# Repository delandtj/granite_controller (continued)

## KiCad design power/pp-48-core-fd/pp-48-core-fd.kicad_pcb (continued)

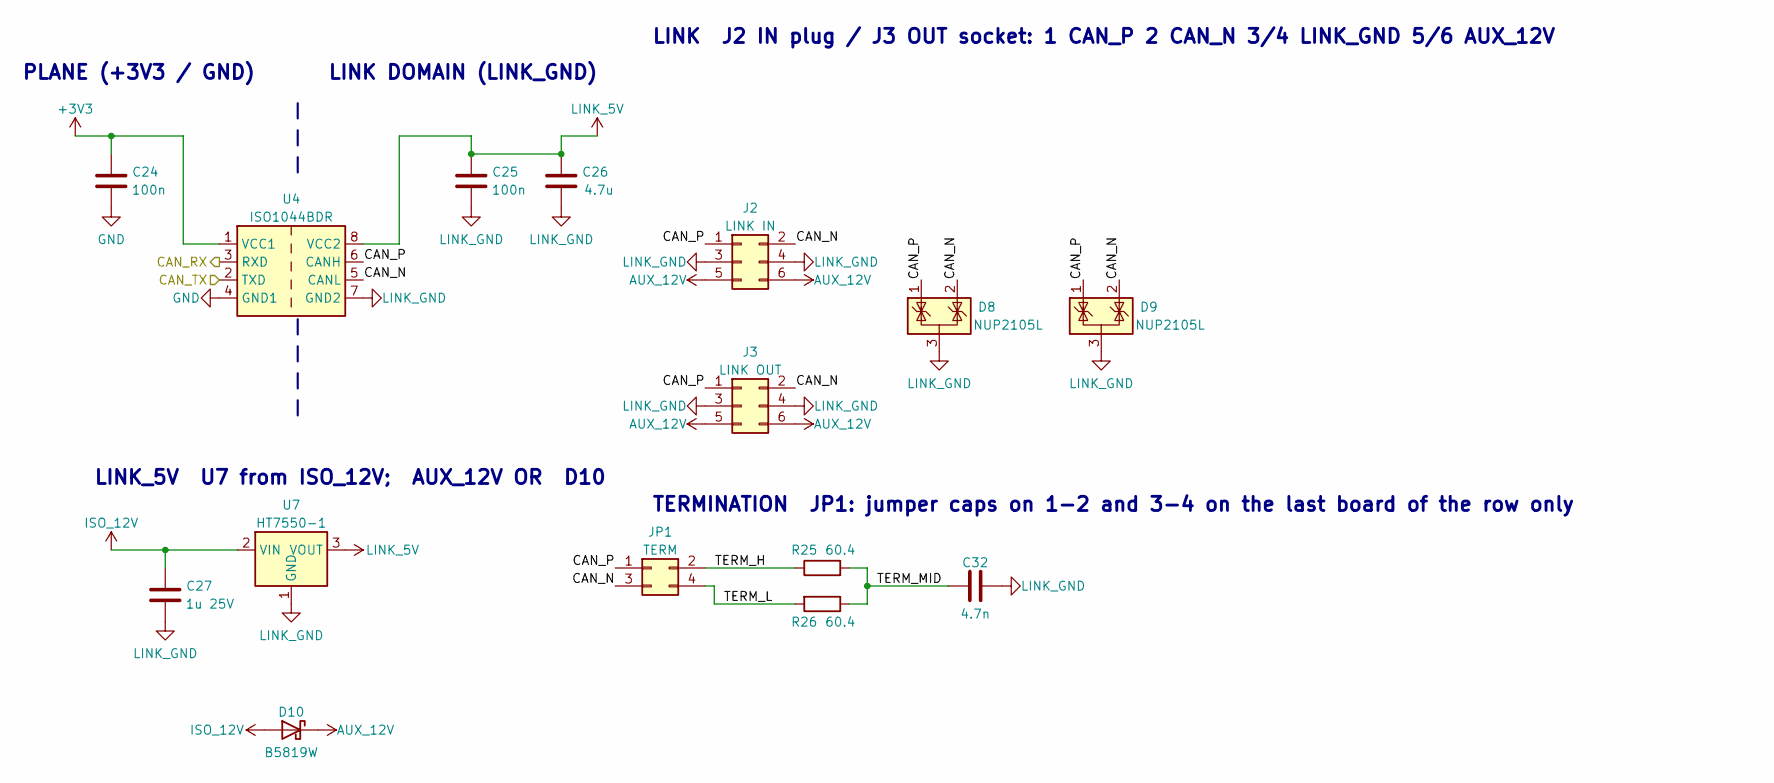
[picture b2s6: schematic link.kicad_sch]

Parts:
C24, C25: 100n; C_0402_1005Metric; MPN Samsung CL05B104KO5NNNC; LCSC C1525
C26: 4.7u; C_0603_1608Metric; MPN Samsung CL10A475KO8NNNC; LCSC C19666
C27: 1u 25V; C_0603_1608Metric; MPN Samsung CL10A105KB8NNNC; LCSC C15849
C32: 4.7n; C_0402_1005Metric; MPN FH 0402B472K500NT; LCSC C1538
D8, D9: NUP2105L; SOT-23; MPN onsemi NUP2105LT1G; LCSC C14486
D10: B5819W; D_SOD-123; MPN SL B5819W; LCSC C8598
J2: LINK IN; PinHeader_2x03_P2.54mm_Horizontal; MPN CJT A2541WR-2x3P; LCSC C239334
J3: LINK OUT; PinSocket_2x03_P2.54mm_Horizontal; MPN CJT A2541HWR-2x3P; LCSC C5333425
JP1: TERM; PinHeader_2x02_P2.54mm_Vertical; MPN XFCN PZ254V-12-4P; LCSC C492419
R25, R26: 60.4; R_0603_1608Metric; MPN Yageo AC0603FR-0760R4L; LCSC C144645
U4: ISO1044BDR; SOIC-8_3.9x4.9mm_P1.27mm; MPN TI ISO1044BDR; LCSC C2878225
U7: HT7550-1; SOT-89-3; MPN Holtek HT7550-1; LCSC C16106

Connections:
+3V3: C24.1, U4.1 (VCC1); also elsewhere on the board
/CAN_RX: U4.3 (RXD); also elsewhere on the board
/CAN_TX: U4.2 (TXD); also elsewhere on the board
/Link/CAN_N: D8.2 (K), D9.2 (K), J2.2, J3.2, JP1.3, U4.5 (CANL)
/Link/CAN_P: D8.1 (K), D9.1 (K), J2.1, J3.1, JP1.1, U4.6 (CANH)
/Link/TERM_H: JP1.2, R25.1
/Link/TERM_L: JP1.4, R26.2
/Link/TERM_MID: C32.1, R25.2, R26.1
AUX_12V: D10.1 (K), J2.5, J2.6, J3.5, J3.6
GND: C24.2, U4.4 (GND1); also elsewhere on the board
ISO_12V: C27.1, D10.2 (A), U7.2 (VIN); also elsewhere on the board
LINK_5V: C25.1, C26.1, U4.8 (VCC2), U7.3 (VOUT)
LINK_GND: C25.2, C26.2, C27.2, C32.2, D8.3 (A), D9.3 (A), J2.3, J2.4, J3.3, J3.4, U4.7 (GND2), U7.1 (GND); also elsewhere on the board

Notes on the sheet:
LINK_5V U7 from ISO_12V; AUX_12V OR D10
PLANE (+3V3 / GND)
LINK DOMAIN (LINK_GND)
LINK J2 IN plug / J3 OUT socket: 1 CAN_P 2 CAN_N 3/4 LINK_GND 5/6 AUX_12V
TERMINATION JP1: jumper caps on 1-2 and 3-4 on the last board of the row only

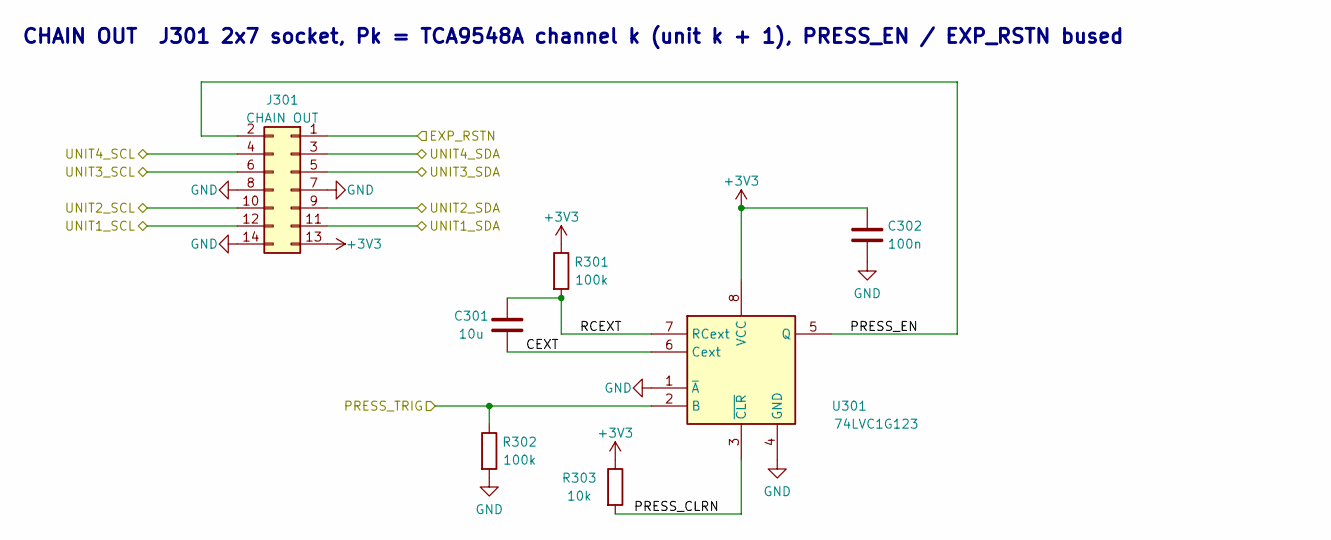
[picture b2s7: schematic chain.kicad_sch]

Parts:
C301: 10u; C_0805_2012Metric; LCSC C15850
C302: 100n; C_0402_1005Metric; LCSC C1525
J301: CHAIN OUT; PinSocket_2x07_P2.54mm_Horizontal; MPN CJT A2541HWR-2x7P; LCSC C19100281
R301, R302: 100k; R_0402_1005Metric; LCSC C25741
R303: 10k; R_0402_1005Metric; LCSC C25744
U301: 74LVC1G123; SSOP-8_2.95x2.8mm_P0.65mm; MPN TI SN74LVC1G123DCTR; LCSC C123302

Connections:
+3V3: C302.1, J301.13, R301.1, R303.1, U301.8 (VCC); also elsewhere on the board
/Chain/CEXT: C301.2, U301.6 (Cext)
/Chain/PRESS_CLRN: R303.2, U301.3 (~CLR)
/Chain/PRESS_EN: J301.2, U301.5 (Q)
/Chain/RCEXT: C301.1, R301.2, U301.7 (RCext)
/EXP_RSTN: J301.1; also elsewhere on the board
/PRESS_TRIG: R302.1, U301.2 (B); also elsewhere on the board
/UNIT1_SCL: J301.12; also elsewhere on the board
/UNIT1_SDA: J301.11; also elsewhere on the board
/UNIT2_SCL: J301.10; also elsewhere on the board
/UNIT2_SDA: J301.9; also elsewhere on the board
/UNIT3_SCL: J301.6; also elsewhere on the board
/UNIT3_SDA: J301.5; also elsewhere on the board
/UNIT4_SCL: J301.4; also elsewhere on the board
/UNIT4_SDA: J301.3; also elsewhere on the board
GND: C302.2, J301.7, J301.8, J301.14, R302.2, U301.1 (~A), U301.4 (GND); also elsewhere on the board

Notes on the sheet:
CHAIN OUT J301 2x7 socket, Pk = TCA9548A channel k (unit k + 1), PRESS_EN / EXP_RSTN bused

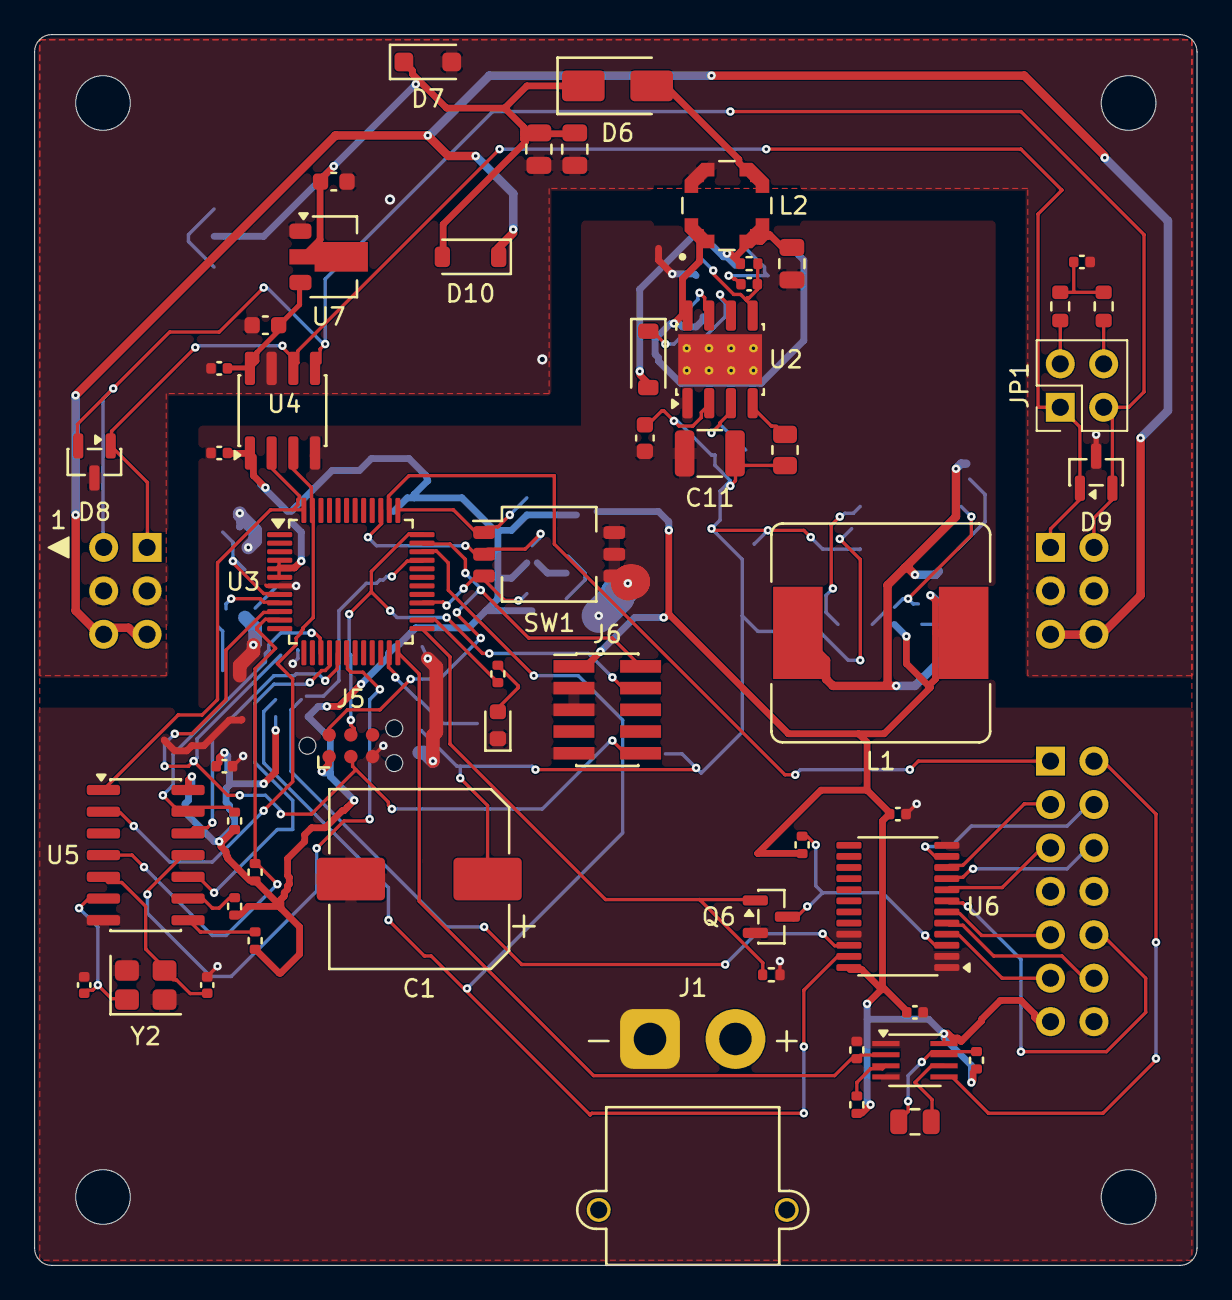
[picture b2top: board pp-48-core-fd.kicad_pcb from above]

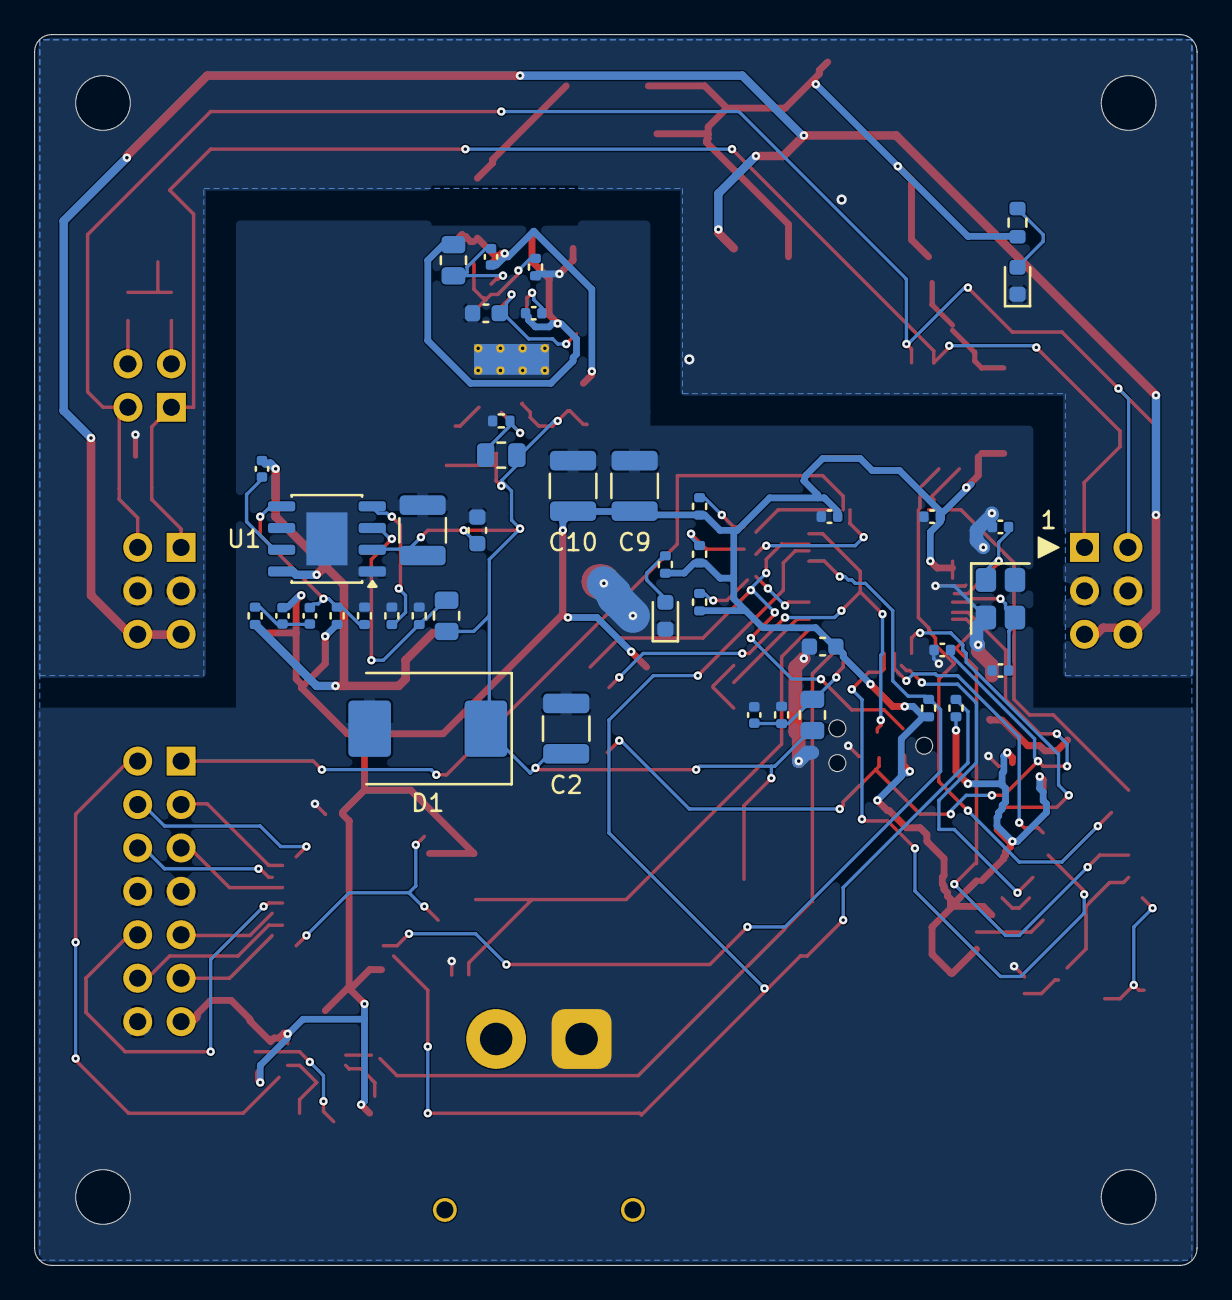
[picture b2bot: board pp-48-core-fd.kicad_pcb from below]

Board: 4 copper layers, 68.0 x 72.0 mm, 104 parts (45 on the bottom side), 69 nets.

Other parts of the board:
H1, H2, H3, H4: MountingHole_3.2mm_M3

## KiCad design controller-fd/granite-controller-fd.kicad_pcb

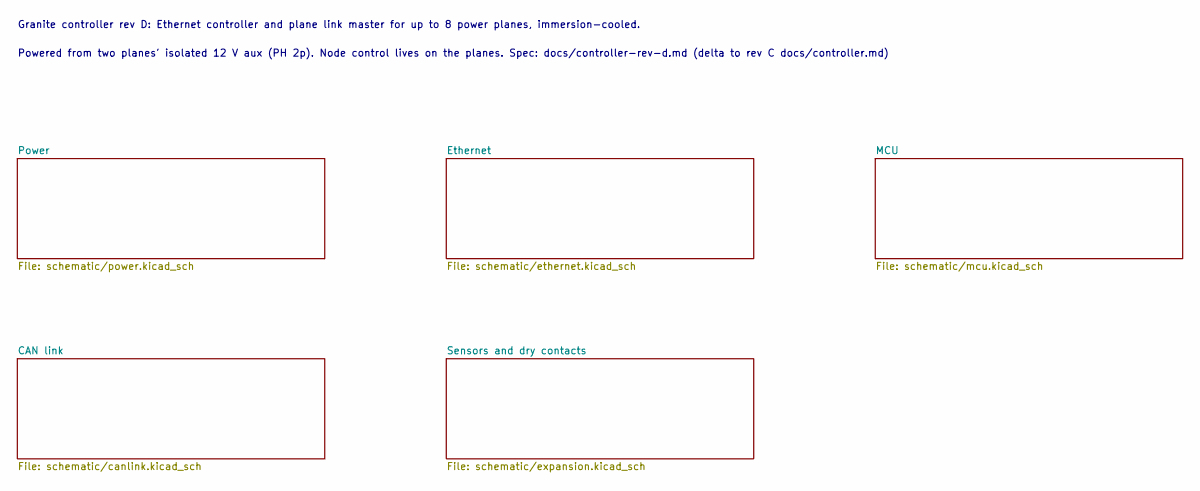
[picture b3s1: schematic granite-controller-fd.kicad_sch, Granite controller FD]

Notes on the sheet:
Granite controller rev D: Ethernet controller and plane link master for up to 8 power planes, immersion-cooled.
Powered from two planes' isolated 12 V aux (PH 2p). Node control lives on the planes. Spec: docs/controller-rev-d.md (delta to rev C docs/controller.md)

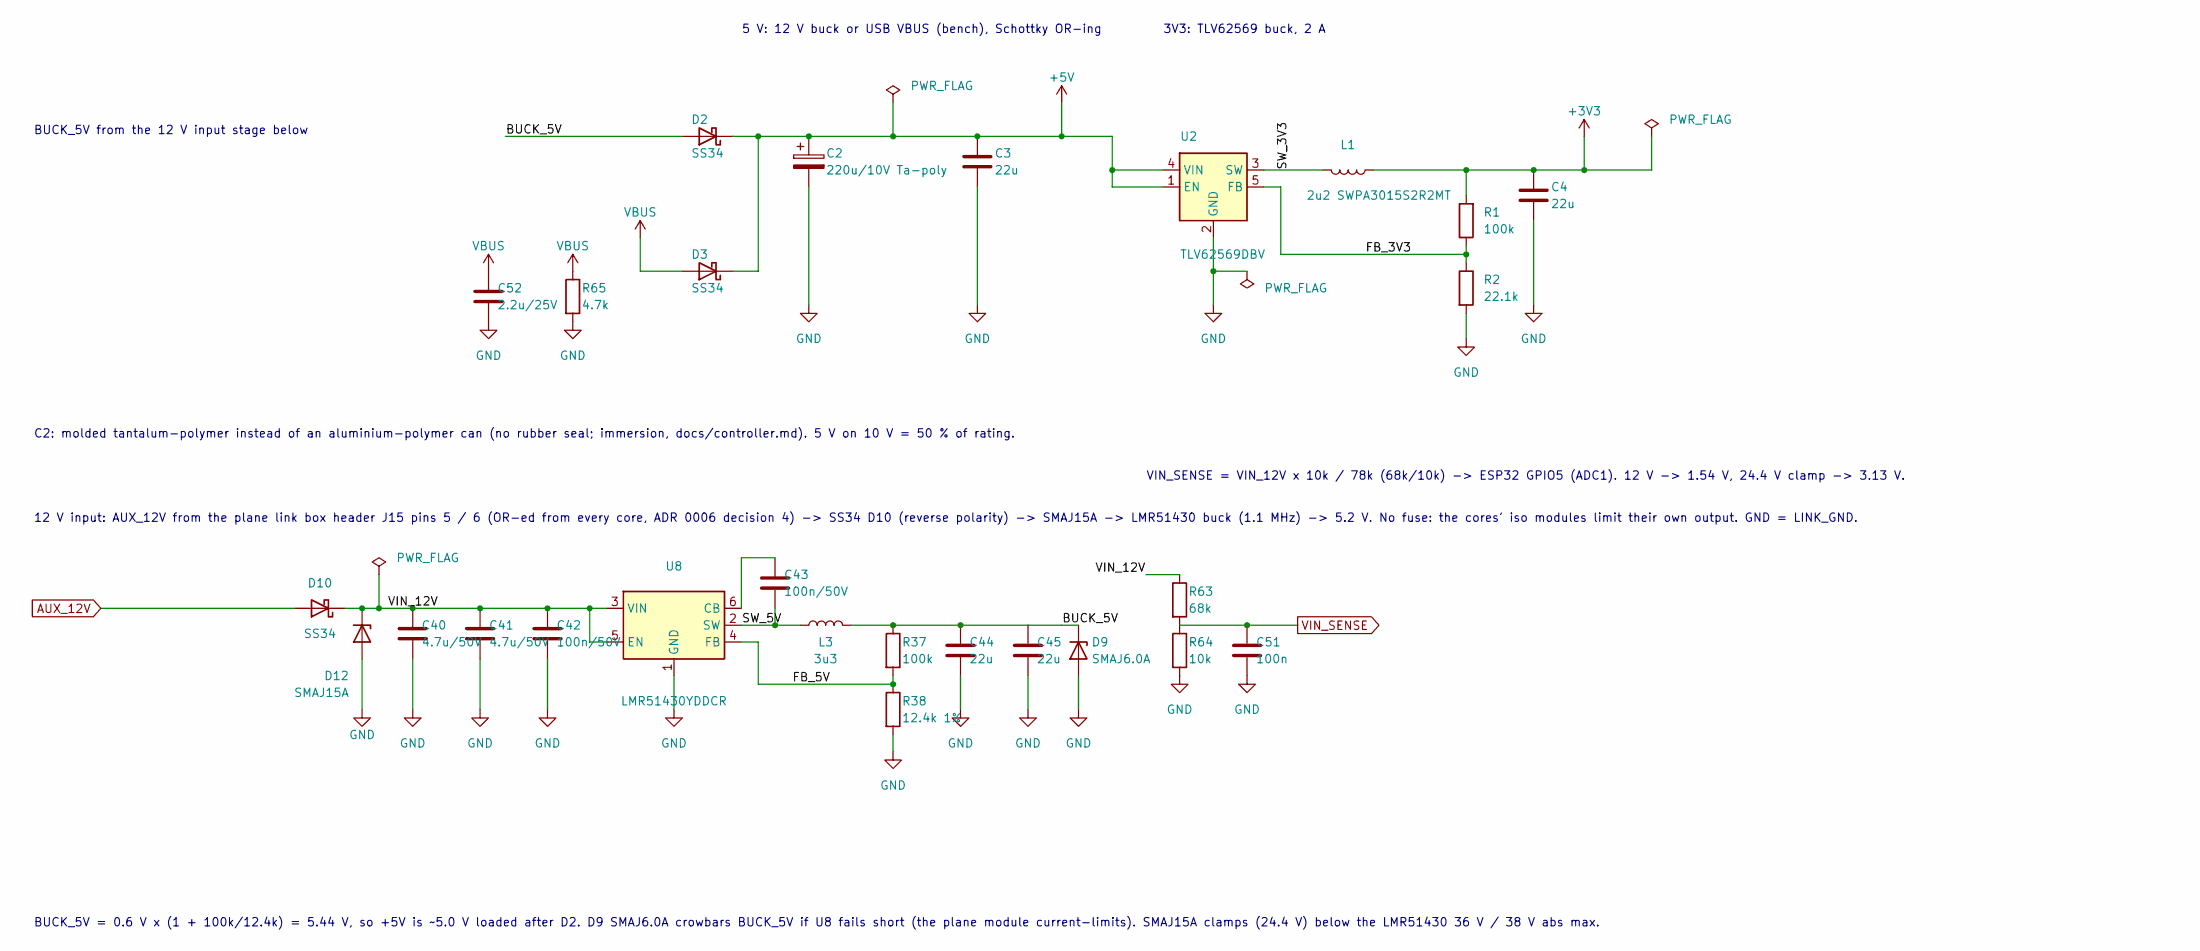
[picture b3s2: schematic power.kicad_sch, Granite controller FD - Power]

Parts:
C2: 220u/10V Ta-poly; CP_EIA-7343-31_Kemet-D; MPN T520D227M010ATE018; LCSC C116742
C3, C4, C44, C45: 22u; C_0805_2012Metric; MPN CL21A226MAQNNNE; LCSC C45783
C40, C41: 4.7u/50V; C_1206_3216Metric; MPN 1206B475K500NT; LCSC C29823
C42, C43: 100n/50V; C_0402_1005Metric; MPN CL05B104KB54PNC; LCSC C307331
C51: 100n; C_0402_1005Metric; MPN CL05B104KO5NNNC; LCSC C1525
C52: 2.2u/25V; C_0603_1608Metric; MPN CL10A225KA8NNNC; LCSC C57895
D2, D3, D10: SS34; D_SMA; MPN SS34; LCSC C8678
D9: SMAJ6.0A; D_SMA; MPN SMAJ6.0A; LCSC C364284
D12: SMAJ15A; D_SMA; MPN SMAJ15A; LCSC C148216
L1: 2u2 SWPA3015S2R2MT; L_Sunlord_SWPA3015S; MPN SWPA3015S2R2MT; LCSC C43389
L3: 3u3; L_Changjiang_FXL0630; MPN FXL0630-3R3-M; LCSC C167219
R1, R37: 100k; R_0402_1005Metric; MPN 0402WGF1003TCE; LCSC C25741
R2: 22.1k; R_0402_1005Metric; MPN RC0402FR-0722K1L; LCSC C163478
R38: 12.4k 1%; R_0402_1005Metric; MPN 0402WGF1242TCE; LCSC C11692
R63: 68k; R_0402_1005Metric; MPN 0402WGF6802TCE; LCSC C36871
R64: 10k; R_0402_1005Metric; MPN 0402WGF1002TCE; LCSC C25744
R65: 4.7k; R_0402_1005Metric; MPN 0402WGF4701TCE; LCSC C25900
U2: TLV62569DBV; SOT-23-5; MPN TLV62569DBVR; LCSC C141836
U8: LMR51430YDDCR; SOT-23-6; MPN LMR51430YDDCR; LCSC C5210749

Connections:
+3V3: C4.1, L1.1, R1.2; also elsewhere on the board
+5V: C2.1, C3.1, D2.1 (K), D3.1 (K), U2.1 (EN), U2.4 (VIN); also elsewhere on the board
/Power/BUCK_5V: C44.1, C45.1, D2.2 (A), D9.1 (K), L3.2, R37.1
/Power/FB_3V3: R1.1, R2.1, U2.5 (FB)
/Power/FB_5V: R37.2, R38.1, U8.4 (FB)
/Power/SW_3V3: L1.2, U2.3 (SW)
/Power/SW_5V: C43.2, L3.1, U8.2 (SW)
/Power/VIN_12V: C40.1, C41.1, C42.1, D10.1 (K), D12.1 (K), R63.1, U8.3 (VIN), U8.5 (EN)
AUX_12V: D10.2 (A); also elsewhere on the board
GND: C2.2, C3.2, C4.2, C40.2, C41.2, C42.2, C44.2, C45.2, C51.2, C52.2, D9.2 (A), D12.2 (A), R2.2, R38.2, R64.2, R65.2, U2.2 (GND), U8.1 (GND); also elsewhere on the board
unnamed: C43.1, U8.6 (CB)
VBUS: C52.1, D3.2 (A), R65.1; also elsewhere on the board
VIN_SENSE: C51.1, R63.2, R64.1; also elsewhere on the board

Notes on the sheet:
5 V: 12 V buck or USB VBUS (bench), Schottky OR-ing
3V3: TLV62569 buck, 2 A
BUCK_5V from the 12 V input stage below
12 V input: AUX_12V from the plane link box header J15 pins 5 / 6 (OR-ed from every core, ADR 0006 decision 4) -> SS34 D10 (reverse polarity) -> SMAJ15A -> LMR51430 buck (1.1 MHz) -> 5.2 V. No fuse: the cores' iso modules limit their own output. GND = LINK_GND.
BUCK_5V = 0.6 V x (1 + 100k/12.4k) = 5.44 V, so +5V is ~5.0 V loaded after D2. D9 SMAJ6.0A crowbars BUCK_5V if U8 fails short (the plane module current-limits). SMAJ15A clamps (24.4 V) below the LMR51430 36 V / 38 V abs max.
C2: molded tantalum-polymer instead of an aluminium-polymer can (no rubber seal; immersion, docs/controller.md). 5 V on 10 V = 50 % of rating.
VIN_SENSE = VIN_12V x 10k / 78k (68k/10k) -> ESP32 GPIO5 (ADC1). 12 V -> 1.54 V, 24.4 V clamp -> 3.13 V.

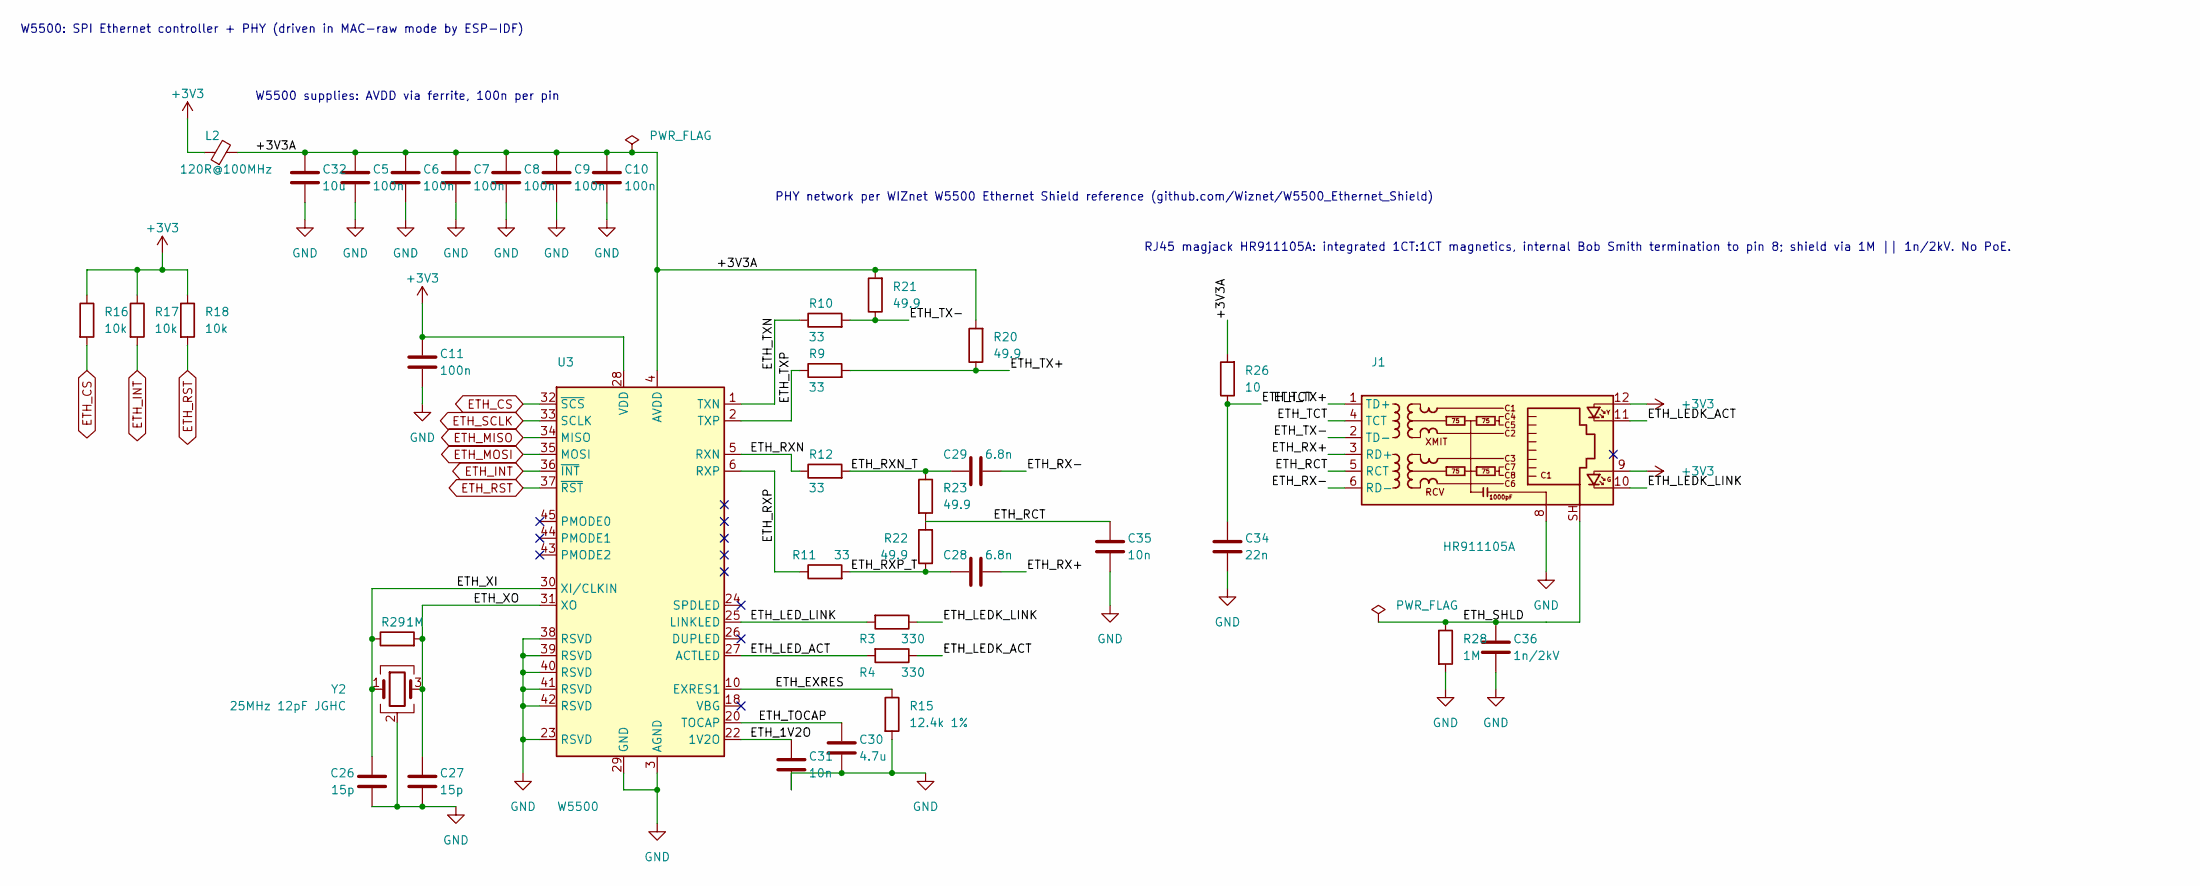
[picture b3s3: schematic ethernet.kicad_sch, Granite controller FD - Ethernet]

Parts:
C5, C6, C7, C8, C9, C10, C11: 100n; C_0402_1005Metric; MPN CL05B104KO5NNNC; LCSC C1525
C26, C27: 15p; C_0402_1005Metric; MPN 0402CG150J500NT; LCSC C1548
C28, C29: 6.8n; C_0402_1005Metric; MPN CC0402KRX7R9BB682; LCSC C93654
C30: 4.7u; C_0603_1608Metric; MPN CL10A475KO8NNNC; LCSC C19666
C31, C35: 10n; C_0402_1005Metric; MPN CL05B103KB5NNNC; LCSC C15195
C32: 10u; C_0805_2012Metric; MPN CL21A106KAYNNNE; LCSC C15850
C34: 22n; C_0402_1005Metric; MPN 0402B223K500NT; LCSC C1532
C36: 1n/2kV; C_1812_4532Metric; MPN CC1812KKX7RDBB102; LCSC C118019
J1: HR911105A; RJ45_Hanrun_HR911105A_Horizontal; MPN HR911105A; LCSC C12074
L2: 120R@100MHz; L_0603_1608Metric; MPN BLM18PG121SN1D; LCSC C14709
R3, R4: 330; R_0402_1005Metric; MPN 0402WGF3300TCE; LCSC C25104
R9, R10, R11, R12: 33; R_0402_1005Metric; MPN 0402WGF330JTCE; LCSC C25105
R15: 12.4k 1%; R_0402_1005Metric; MPN 0402WGF1242TCE; LCSC C11692
R16, R17, R18: 10k; R_0402_1005Metric; MPN 0402WGF1002TCE; LCSC C25744
R20, R21, R22, R23: 49.9; R_0402_1005Metric; MPN 0402WGF499JTCE; LCSC C25120
R26: 10; R_0402_1005Metric; MPN 0402WGF100JTCE; LCSC C25077
R28: 1M; R_0603_1608Metric; MPN 0603WAF1004T5E; LCSC C22935
R29: 1M; R_0402_1005Metric; MPN 0402WGF1004TCE; LCSC C26083
U3: W5500; LQFP-48_7x7mm_P0.5mm; MPN W5500; LCSC C32843
Y2: 25MHz 12pF JGHC; Crystal_SMD_Abracon_ABM8G-4Pin_3.2x2.5mm; MPN S3225000121060; LCSC C390773

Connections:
+3V3: C11.1, J1.9, J1.12, L2.1, R16.1, R17.1, R18.1, U3.28 (VDD); also elsewhere on the board
/Ethernet/+3V3A: C5.1, C6.1, C7.1, C8.1, C9.1, C10.1, C32.1, L2.2, R20.2, R21.2, R26.2, U3.4 (AVDD), U3.8 (AVDD), U3.11 (AVDD), U3.15 (AVDD), U3.17 (AVDD), U3.21 (AVDD)
/Ethernet/ETH_1V2O: C31.1, U3.22 (1V2O)
/Ethernet/ETH_EXRES: R15.1, U3.10 (EXRES1)
/Ethernet/ETH_LEDK_ACT: J1.11, R4.1
/Ethernet/ETH_LEDK_LINK: J1.10, R3.1
/Ethernet/ETH_LED_ACT: R4.2, U3.27 (ACTLED)
/Ethernet/ETH_LED_LINK: R3.2, U3.25 (LINKLED)
/Ethernet/ETH_RCT: C35.1, J1.5 (RCT), R22.2, R23.2
/Ethernet/ETH_RX+: C28.2, J1.3 (RD+)
/Ethernet/ETH_RX-: C29.2, J1.6 (RD-)
/Ethernet/ETH_RXN: R12.1, U3.5 (RXN)
/Ethernet/ETH_RXN_T: C29.1, R12.2, R23.1
/Ethernet/ETH_RXP: R11.1, U3.6 (RXP)
/Ethernet/ETH_RXP_T: C28.1, R11.2, R22.1
/Ethernet/ETH_SHLD: C36.1, J1.SH, R28.1
/Ethernet/ETH_TCT: C34.1, J1.4 (TCT), R26.1
/Ethernet/ETH_TOCAP: C30.1, U3.20 (TOCAP)
/Ethernet/ETH_TX+: J1.1 (TD+), R9.2, R20.1
/Ethernet/ETH_TX-: J1.2 (TD-), R10.2, R21.1
/Ethernet/ETH_TXN: R10.1, U3.1 (TXN)
/Ethernet/ETH_TXP: R9.1, U3.2 (TXP)
/Ethernet/ETH_XI: C26.1, R29.1, U3.30 (XI/CLKIN), Y2.1
/Ethernet/ETH_XO: C27.1, R29.2, U3.31 (XO), Y2.3
ETH_CS: R16.2, U3.32 (~SCS); also elsewhere on the board
ETH_INT: R17.2, U3.36 (~INT); also elsewhere on the board
ETH_MISO: U3.34 (MISO); also elsewhere on the board
ETH_MOSI: U3.35 (MOSI); also elsewhere on the board
ETH_RST: R18.2, U3.37 (~RST); also elsewhere on the board
ETH_SCLK: U3.33 (SCLK); also elsewhere on the board
GND: C5.2, C6.2, C7.2, C8.2, C9.2, C10.2, C11.2, C26.2, C27.2, C30.2, C31.2, C32.2, C34.2, C35.2, C36.2, J1.8, R15.2, R28.2, U3.3 (AGND), U3.9 (AGND), U3.14 (AGND), U3.16 (AGND), U3.19 (AGND), U3.23 (RSVD), U3.29 (GND), U3.38 (RSVD), U3.39 (RSVD), U3.40 (RSVD), U3.41 (RSVD), U3.42 (RSVD), U3.48 (AGND), Y2.2 (G), Y2.4 (G); also elsewhere on the board

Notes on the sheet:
W5500: SPI Ethernet controller + PHY (driven in MAC-raw mode by ESP-IDF)
W5500 supplies: AVDD via ferrite, 100n per pin
PHY network per WIZnet W5500 Ethernet Shield reference (github.com/Wiznet/W5500_Ethernet_Shield)
RJ45 magjack HR911105A: integrated 1CT:1CT magnetics, internal Bob Smith termination to pin 8; shield via 1M || 1n/2kV. No PoE.

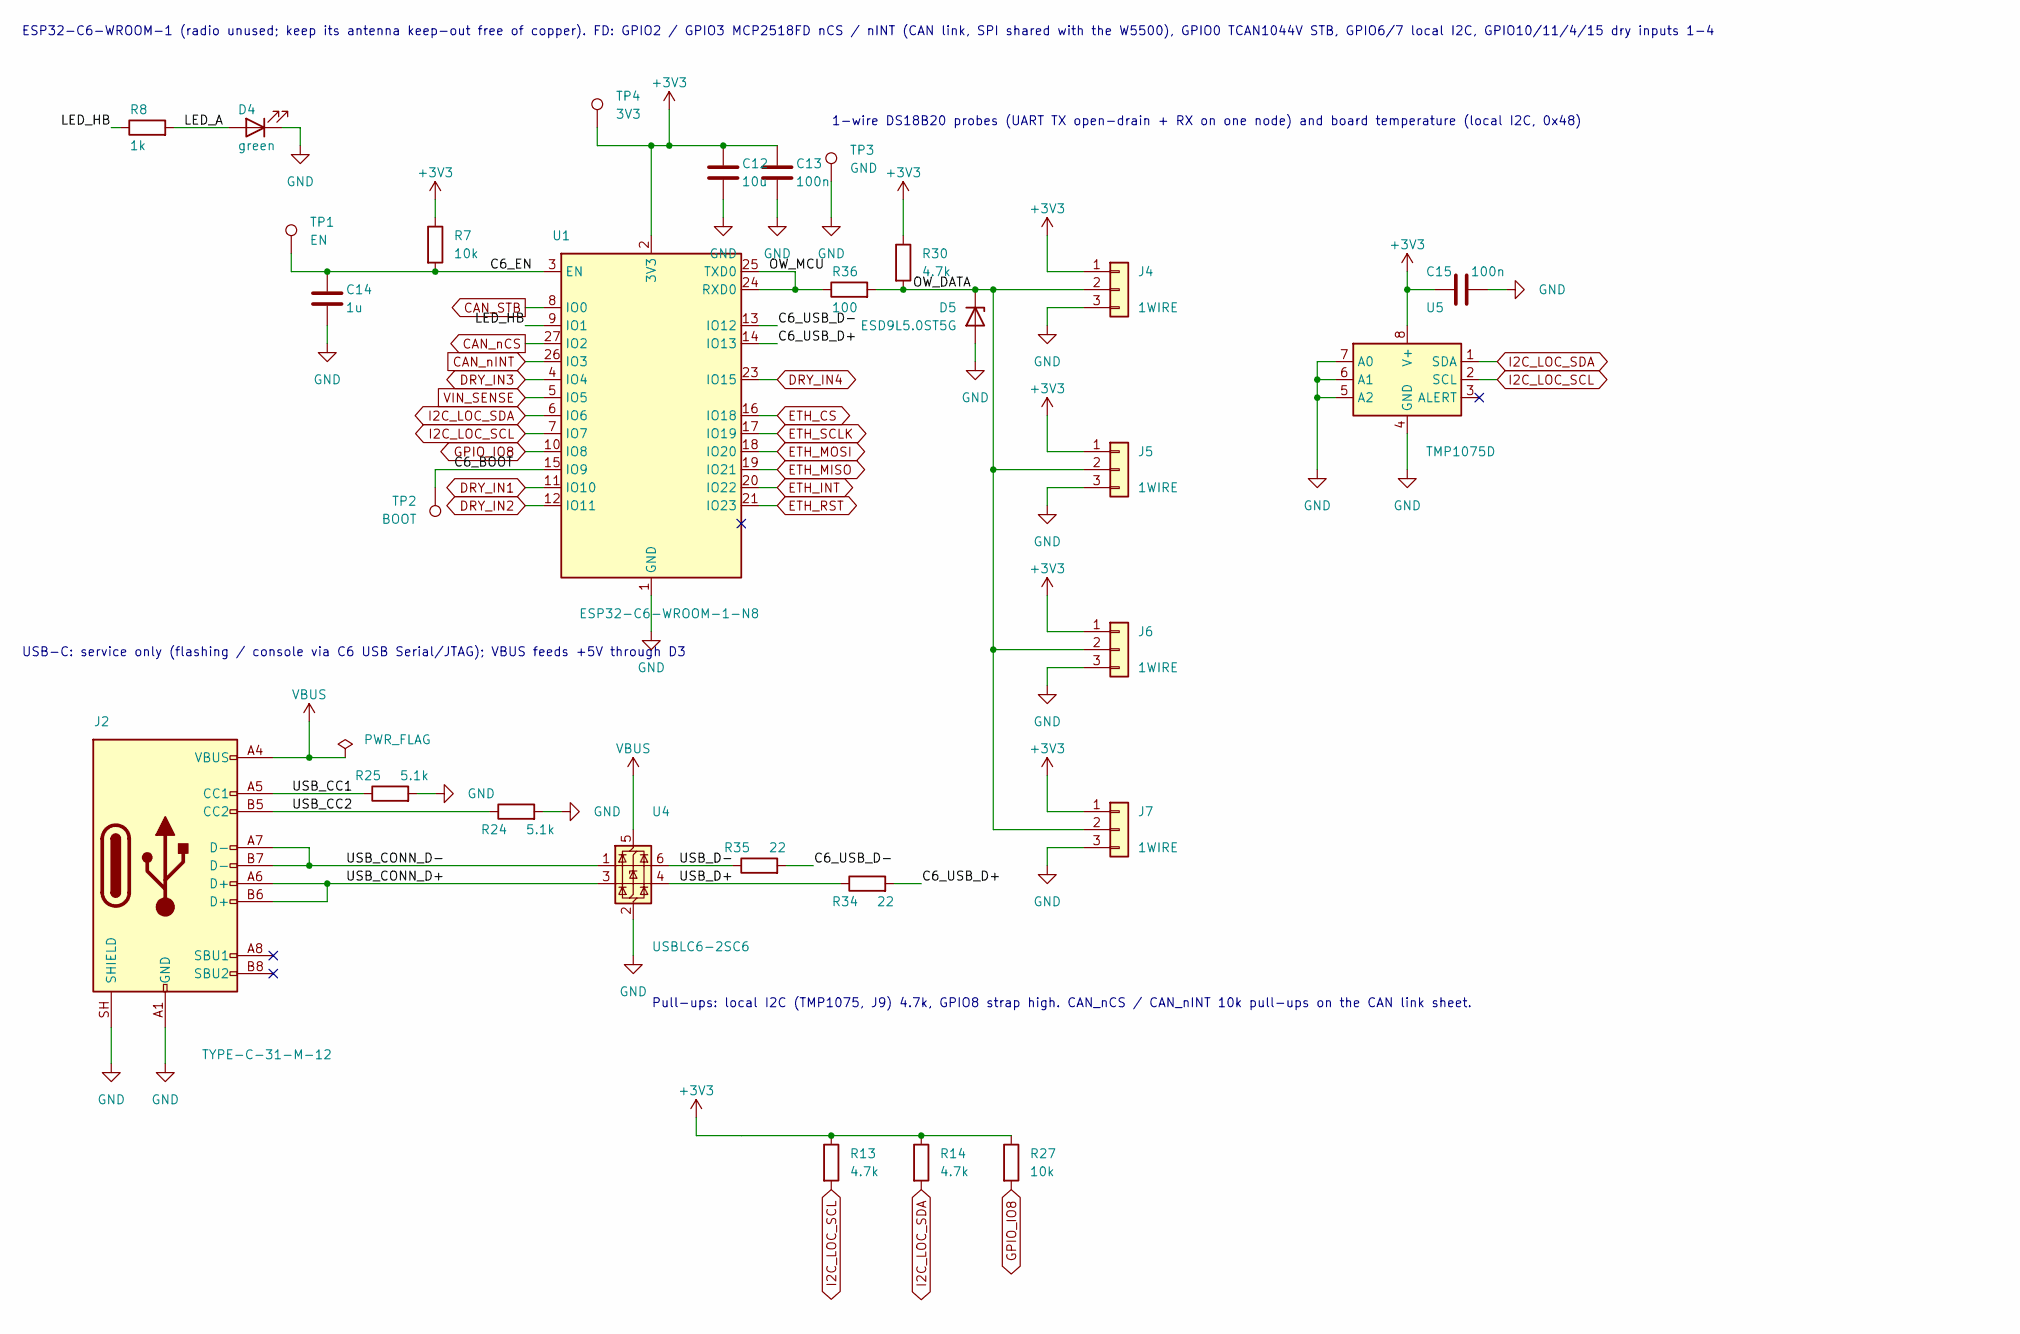
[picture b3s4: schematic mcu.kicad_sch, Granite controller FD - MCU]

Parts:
C12: 10u; C_0805_2012Metric; MPN CL21A106KAYNNNE; LCSC C15850
C13, C15: 100n; C_0402_1005Metric; MPN CL05B104KO5NNNC; LCSC C1525
C14: 1u; C_0603_1608Metric; MPN CL10A105KB8NNNC; LCSC C15849
D4: green; LED_0603_1608Metric; MPN KT-0603G; LCSC C12624
D5: ESD9L5.0ST5G; D_SOD-923; MPN ESD9L5.0ST5G; LCSC C82326
J2: TYPE-C-31-M-12; USB_C_Receptacle_HRO_TYPE-C-31-M-12; MPN TYPE-C-31-M-12; LCSC C165948
J4, J5, J6, J7: 1WIRE; JST_PH_B3B-PH-K_1x03_P2.00mm_Vertical; MPN B3B-PH-K-S(LF)(SN); LCSC C131339
R7, R27: 10k; R_0402_1005Metric; MPN 0402WGF1002TCE; LCSC C25744
R8: 1k; R_0402_1005Metric; MPN 0402WGF1001TCE; LCSC C11702
R13, R14, R30: 4.7k; R_0402_1005Metric; MPN 0402WGF4701TCE; LCSC C25900
R24, R25: 5.1k; R_0402_1005Metric; MPN 0402WGF5101TCE; LCSC C25905
R34, R35: 22; R_0402_1005Metric; MPN 0402WGF220JTCE; LCSC C25092
R36: 100; R_0603_1608Metric; MPN 0603WAF1000T5E; LCSC C22775
TP1: EN; TestPoint_Pad_D1.5mm
TP2: BOOT; TestPoint_Pad_D1.5mm
TP3: GND; TestPoint_Pad_D1.5mm
TP4: 3V3; TestPoint_Pad_D1.5mm
U1: ESP32-C6-WROOM-1-N8; ESP32-C6-WROOM-1; MPN ESP32-C6-WROOM-1-N8; LCSC C5366877
U4: USBLC6-2SC6; SOT-23-6; MPN USBLC6-2SC6; LCSC C7519
U5: TMP1075D; SOIC-8_3.9x4.9mm_P1.27mm; MPN TMP1075DR; LCSC C2878381

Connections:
+3V3: C12.1, C13.1, C15.1, J4.1, J5.1, J6.1, J7.1, R7.1, R13.1, R14.1, R27.1, R30.1, TP4.1, U1.2 (3V3), U5.8 (V+); also elsewhere on the board
/MCU/C6_BOOT: TP2.1, U1.15 (IO9)
/MCU/C6_EN: C14.1, R7.2, TP1.1, U1.3 (EN)
/MCU/C6_USB_D+: R34.2, U1.14 (IO13)
/MCU/C6_USB_D-: R35.2, U1.13 (IO12)
/MCU/LED_A: D4.2 (A), R8.2
/MCU/LED_HB: R8.1, U1.9 (IO1)
/MCU/OW_DATA: D5.1 (K), J4.2, J5.2, J6.2, J7.2, R30.2, R36.2
/MCU/OW_MCU: R36.1, U1.24 (RXD0), U1.25 (TXD0)
/MCU/USB_CC1: J2.A5 (CC1), R25.1
/MCU/USB_CC2: J2.B5 (CC2), R24.1
/MCU/USB_CONN_D+: J2.A6 (D+), J2.B6 (D+), U4.3 (I/O2)
/MCU/USB_CONN_D-: J2.A7 (D-), J2.B7 (D-), U4.1 (I/O1)
/MCU/USB_D+: R34.1, U4.4 (I/O2)
/MCU/USB_D-: R35.1, U4.6 (I/O1)
CAN_STB: U1.8 (IO0); also elsewhere on the board
CAN_nCS: U1.27 (IO2); also elsewhere on the board
CAN_nINT: U1.26 (IO3); also elsewhere on the board
DRY_IN1: U1.11 (IO10); also elsewhere on the board
DRY_IN2: U1.12 (IO11); also elsewhere on the board
DRY_IN3: U1.4 (IO4); also elsewhere on the board
DRY_IN4: U1.23 (IO15); also elsewhere on the board
ETH_CS: U1.16 (IO18); also elsewhere on the board
ETH_INT: U1.20 (IO22); also elsewhere on the board
ETH_MISO: U1.19 (IO21); also elsewhere on the board
ETH_MOSI: U1.18 (IO20); also elsewhere on the board
ETH_RST: U1.21 (IO23); also elsewhere on the board
ETH_SCLK: U1.17 (IO19); also elsewhere on the board
GND: C12.2, C13.2, C14.2, C15.2, D4.1 (K), D5.2 (A), J2.A1 (GND), J2.A12 (GND), J2.B1 (GND), J2.B12 (GND), J2.SH (SHIELD), J4.3, J5.3, J6.3, J7.3, R24.2, R25.2, TP3.1, U1.1 (GND), U1.28 (GND), U1.29 (GND), U4.2 (GND), U5.4 (GND), U5.5 (A2), U5.6 (A1), U5.7 (A0); also elsewhere on the board
GPIO_IO8: R27.2, U1.10 (IO8)
I2C_LOC_SCL: R13.2, U1.7 (IO7), U5.2 (SCL); also elsewhere on the board
I2C_LOC_SDA: R14.2, U1.6 (IO6), U5.1 (SDA); also elsewhere on the board
VBUS: J2.A4 (VBUS), J2.A9 (VBUS), J2.B4 (VBUS), J2.B9 (VBUS), U4.5 (VBUS); also elsewhere on the board
VIN_SENSE: U1.5 (IO5); also elsewhere on the board

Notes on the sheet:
ESP32-C6-WROOM-1 (radio unused; keep its antenna keep-out free of copper). FD: GPIO2 / GPIO3 MCP2518FD nCS / nINT (CAN link, SPI shared with the W5500), GPIO0 TCAN1044V STB, GPIO6/7 local I2C, GPIO10/11/4/15 dry inputs 1-4
1-wire DS18B20 probes (UART TX open-drain + RX on one node) and board temperature (local I2C, 0x48)
USB-C: service only (flashing / console via C6 USB Serial/JTAG); VBUS feeds +5V through D3
Pull-ups: local I2C (TMP1075, J9) 4.7k, GPIO8 strap high. CAN_nCS / CAN_nINT 10k pull-ups on the CAN link sheet.
